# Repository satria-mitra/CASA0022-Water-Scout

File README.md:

<h1 align="center">Water Scout: A LoRaWAN-Based Water Height Monitoring and Visualization System for Urban Waterways</h1>

A dissertation for an [MSc Connected Environments](https://www.ucl.ac.uk/prospective-students/graduate/taught-degrees/connected-environments-msc)
<p>Centre for Advanced Spatial Analysis, Bartlett Faculty of the Built Environment</p>
<p>University College London </p>

##

This project utilised an Arduino 1310 with LoRaWAN communication and Ultrasonic sensor to monitor the water level of the River Lea that flows below the House Mill. The data observed then transmitted to The Things Network and published to MQTT Client. A 3D visualisation web page using WebXR was built to display the water level of The House Mill in 3D scene. The House Mill was created by [Dr. Gai Jorayev ](https://www.ucl.ac.uk/archaeology/people/gai-jorayev) and published on [Sketchfab](https://sketchfab.com/3d-models/house-mill-in-2019-c87dd07ab29f474aa491c88bc6b4956f). [The 3D visualisations web page](https://casa-0022-water-scout.vercel.app/) was hosted in the cloud for accessibility

|                         Water Scout                           |                3D Visualisations                 |
| :----------------------------------------------------------: | :-------------------------------------------: |
|  |  |

## Repository Content Summary

1. **3D Parts**

   This folder includes the 3D printed parts, namely Fusion360 project files and STLs for the enclosures and the 3D objects for the Data Table.

   - [Water Scout Enclosure](</3D Parts/Enclosure>)
   - [Solar Panel](</3D Parts/Solar Panel/>)

2. **Arduino**

   Includes code during calibration mode, and Water Scout device

   - [DYP-A01](/Arduino/DYP-A01)

3. **Schematics**

   The final schematics including PCB Gerber file used for this project. 
   
4. **Docs**

   This folder holds the page for the Water Scout web pages, including device introduction, 3D Visualisation page and VR mode for Connected Environment exhibition

5. **Dashboard**

   The configuration file for Node Red, Influxdb and Grafana 

6. **Supporting Documents**

   The extra files from the dissertation report, including Lab Testing, Deployment Test, and analysis

## Project Overview

<p align="center">Final prototype</p>

## Building

### Used components and tools

Hardware:

* [Arduino MKR WAN 1310](https://docs.arduino.cc/hardware/mkr-wan-1310): microcontroller with LoRa connectivity.
* [DYP-A01](https://www.dypcn.com/high-performance-ultrasonic-precision-rangefinder-dyp-a01-product/): a weatherproof humidity and temperature sensor.
* [Adafruit Solar Charger](https://www.adafruit.com/product/4755): a solar charger module
* [Adafruit Lipo Battery Gauge](https://www.adafruit.com/product/5580)
* [Solar panel](https://coolcomponents.co.uk/products/solar-panel-1-watt): 1 Watt, 10x80 cm.
* 2000 mA 3.7v battery

Software:

 - [InfluxDB](https://www.influxdata.com/)
 - [Telegraf](https://www.influxdata.com/time-series-platform/telegraf/)
 - [Grafana](https://grafana.com/)
 - [Docker Compose](https://docs.docker.com/compose/)

All the software applications are packed into one using Docker

## Results

#### The 3D Visualisations

<p align="center">3D Visualisations scene</p>

Click here for [3D Visualisations](https://casa-0022-water-scout.vercel.app/visualisation.html)

#### VR Mode for exhibition

<p align="center">3D Visualisations scene</p>

Click here for [VR Mode](https://casa-0022-water-scout.vercel.app/arjs.html)

## Credits

This project was built with inspiration and support from several open-source projects and contributions.

Special thanks to [CASA CE](https://github.com/ucl-casa-ce) team especially for the [Artes](https://github.com/ucl-casa-ce/artes) repository which was instrumental in creating the VR mode for the Water Scout project. Portions of the code for the VR mode were adapted and modified from his project.

Additionally, thanks to the open-source communities and contributors behind the following software and tools, which were essential in the development of this project:

- Arduino
- The Things Network
- InfluxDB
- Grafana
- Docker

## License

###### The software side is licensed under MIT License

```
MIT License

Permission is hereby granted, free of charge, to any person obtaining a copy
of this software and associated documentation files (the "Software"), to deal
in the Software without restriction, including without limitation the rights
to use, copy, modify, merge, publish, distribute, sublicense, and/or sell
copies of the Software, and to permit persons to whom the Software is
furnished to do so, subject to the following conditions:

The above copyright notice and this permission notice shall be included in all
copies or substantial portions of the Software.

THE SOFTWARE IS PROVIDED "AS IS", WITHOUT WARRANTY OF ANY KIND, EXPRESS OR
IMPLIED, INCLUDING BUT NOT LIMITED TO THE WARRANTIES OF MERCHANTABILITY,
FITNESS FOR A PARTICULAR PURPOSE AND NONINFRINGEMENT. IN NO EVENT SHALL THE
AUTHORS OR COPYRIGHT HOLDERS BE LIABLE FOR ANY CLAIM, DAMAGES OR OTHER
LIABILITY, WHETHER IN AN ACTION OF CONTRACT, TORT OR OTHERWISE, ARISING FROM,
OUT OF OR IN CONNECTION WITH THE SOFTWARE OR THE USE OR OTHER DEALINGS IN THE
SOFTWARE.
```

###### The hardware side is licensed under CERN License

```
This documentation describes Open Hardware and is licensed under the CERN OHL v. 1.2.

You may redistribute and modify this documentation under the terms of the CERN OHL v.1.2. (http://ohwr.org/cernohl). This documentation is distributed WITHOUT ANY EXPRESS OR IMPLIED WARRANTY, INCLUDING OF MERCHANTABILITY, SATISFACTORY QUALITY AND FITNESS FOR A PARTICULAR PURPOSE. Please see the CERN OHL v.1.2 for applicable conditions
```

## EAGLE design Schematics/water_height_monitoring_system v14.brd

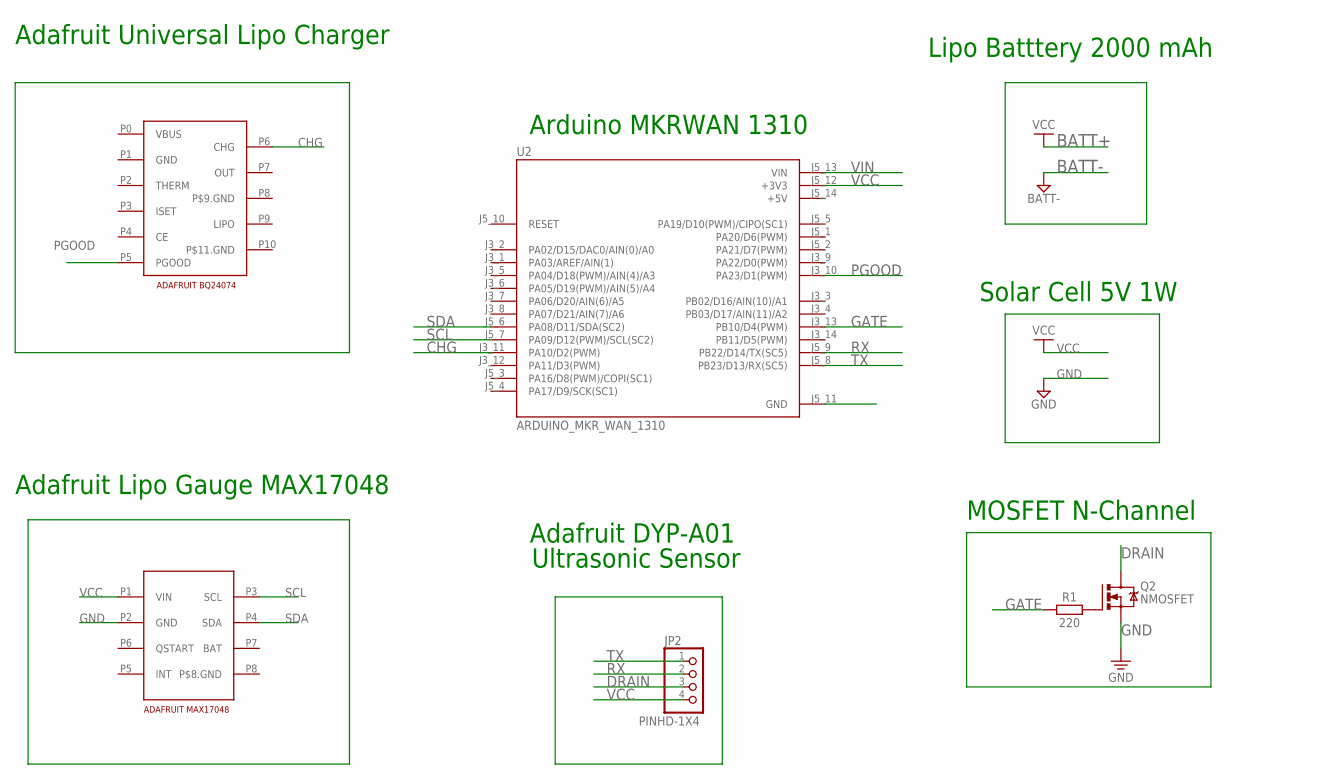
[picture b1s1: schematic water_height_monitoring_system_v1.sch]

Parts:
JP2: PINHD-1X4; 1X04
Q2: NMOSFET; TO220BV
R1: 220; RESAD724W46L381D178B
U2: ARDUINO_MKR_WAN_1310; BOARD_ARDUINO_MKR_WAN_1310
U$2: ADAFRUIT_BQ24074; BQ24074_MODULE
U$3: ADAFRUIT_MAX17048; MAX17048

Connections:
+5V: U2.J5_14 (+5V)
BAT: U$3.P7 (BAT)
CHG: U2.J3_11 (PA10/D2(PWM)), U$2.P6 (CHG)
DRAIN: JP2.3, Q2.D
GATE: R1.1, U2.J3_13 (PB10/D4(PWM))
LIPO: U$2.P9 (LIPO)
unnamed: Q2.G, R1.2
P$8.GND: U$3.P8 (P$8.GND)
P$9.GND: U$2.P8 (P$9.GND)
P$11.GND: U$2.P10 (P$11.GND)
PGOOD: U2.J3_10 (PA23/D1(PWM)), U$2.P5 (PGOOD)
RX: JP2.2, U2.J5_9 (PB22/D14/TX(SC5))
SCL: U2.J5_7 (PA09/D12(PWM)/SCL(SC2)), U$3.P3 (SCL)
SDA: U2.J5_6 (PA08/D11/SDA(SC2)), U$3.P4 (SDA)
TX: JP2.1, U2.J5_8 (PB23/D13/RX(SC5))
VBUS: U$2.P0 (VBUS)
VCC: JP2.4, U2.J5_12 (+3V3), U$3.P1 (VIN)
VIN: U2.J5_13 (VIN)

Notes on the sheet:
Adafruit Universal Lipo Charger
Adafruit Lipo Gauge MAX17048
Arduino MKRWAN 1310
Lipo Batttery 2000 mAh
Solar Cell 5V 1W
MOSFET N-Channel
Adafruit DYP-A01 Ultrasonic Sensor

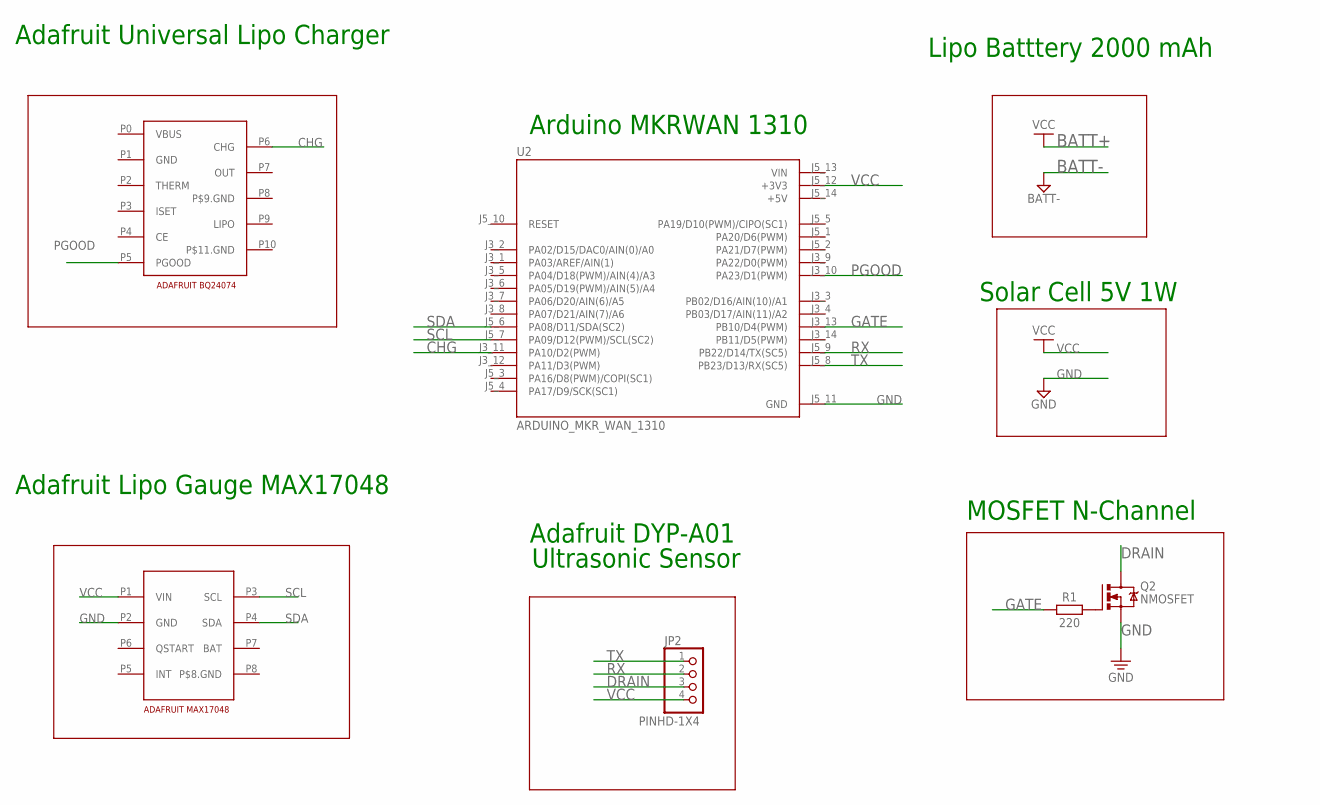
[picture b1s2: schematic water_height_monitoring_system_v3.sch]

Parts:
JP2: PINHD-1X4; 1X04
Q2: NMOSFET; TO220BV
R1: 220; RESAD724W46L381D178B
U2: ARDUINO_MKR_WAN_1310; BOARD_ARDUINO_MKR_WAN_1310
U$2: ADAFRUIT_BQ24074; BQ24074_MODULE
U$3: ADAFRUIT_MAX17048; MAX17048

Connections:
+5V: U2.J5_14 (+5V)
BAT: U$3.P7 (BAT)
CHG: U2.J3_11 (PA10/D2(PWM)), U$2.P6 (CHG)
DRAIN: JP2.3, Q2.D
GATE: R1.1, U2.J3_13 (PB10/D4(PWM))
LIPO: U$2.P9 (LIPO)
unnamed: Q2.G, R1.2
P$8.GND: U$3.P8 (P$8.GND)
P$9.GND: U$2.P8 (P$9.GND)
P$11.GND: U$2.P10 (P$11.GND)
PGOOD: U2.J3_10 (PA23/D1(PWM)), U$2.P5 (PGOOD)
RX: JP2.2, U2.J5_9 (PB22/D14/TX(SC5))
SCL: U2.J5_7 (PA09/D12(PWM)/SCL(SC2)), U$3.P3 (SCL)
SDA: U2.J5_6 (PA08/D11/SDA(SC2)), U$3.P4 (SDA)
TX: JP2.1, U2.J5_8 (PB23/D13/RX(SC5))
VBUS: U$2.P0 (VBUS)
VCC: JP2.4, U2.J5_12 (+3V3), U$3.P1 (VIN)

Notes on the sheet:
Adafruit Universal Lipo Charger
Adafruit Lipo Gauge MAX17048
Arduino MKRWAN 1310
Lipo Batttery 2000 mAh
Solar Cell 5V 1W
MOSFET N-Channel
Adafruit DYP-A01 Ultrasonic Sensor

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
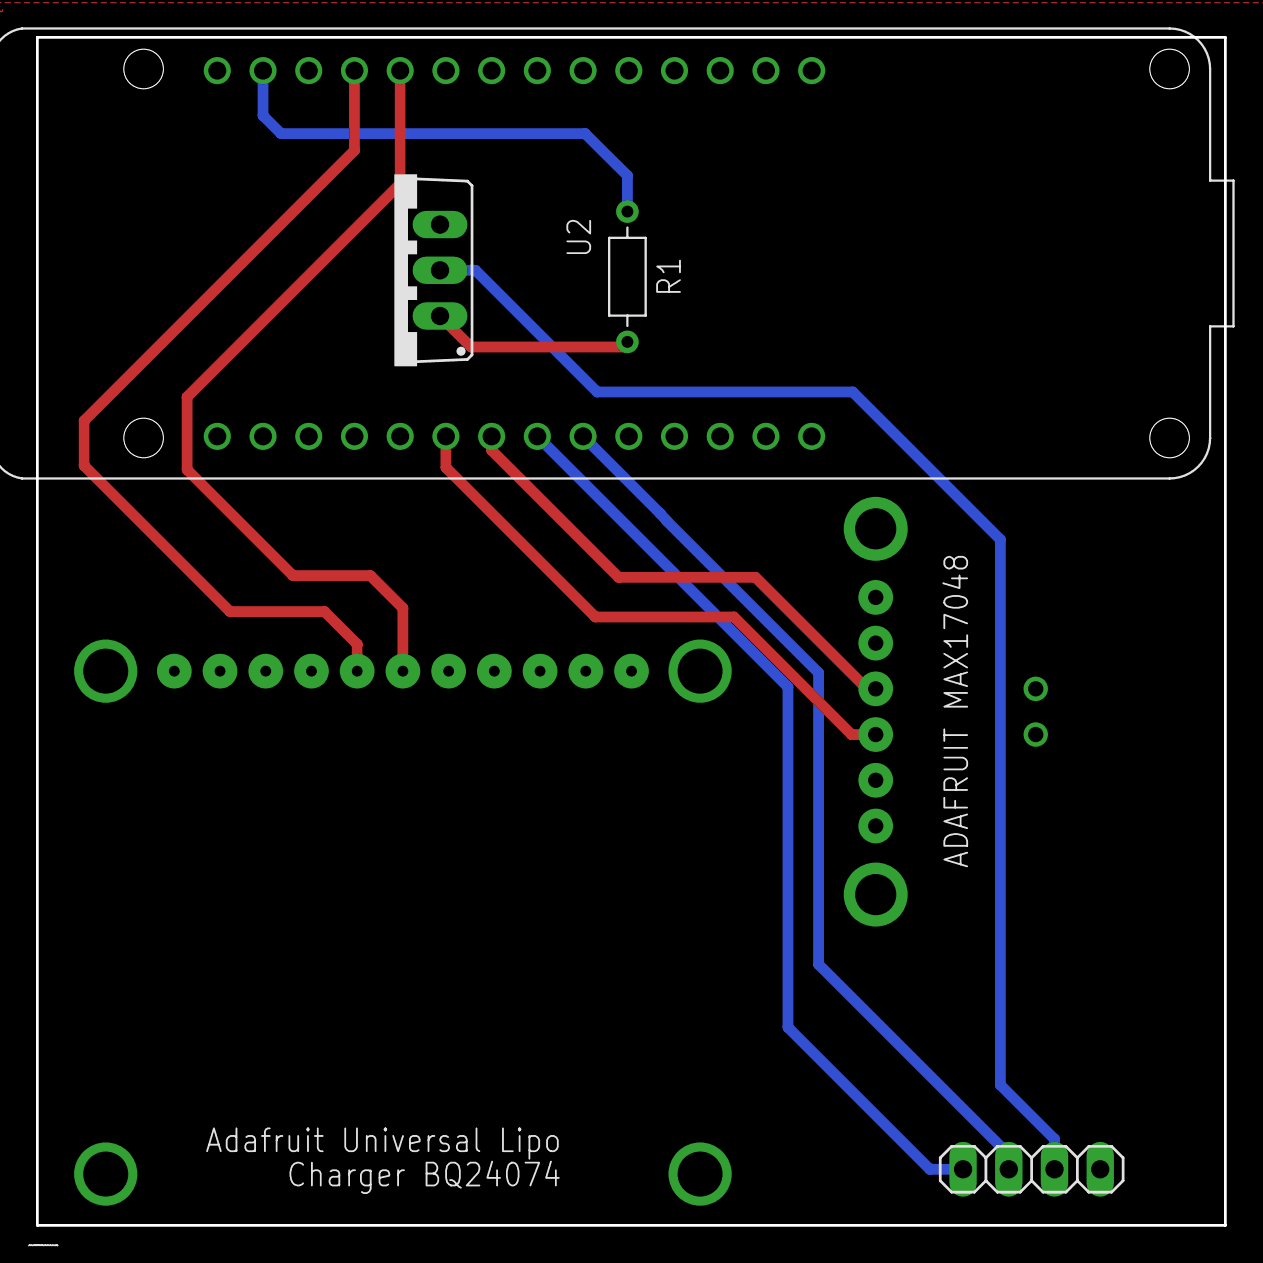
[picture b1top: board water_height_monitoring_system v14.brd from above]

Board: 2 copper layers, 66.0 x 66.0 mm, 6 parts (0 on the bottom side), 11 nets.

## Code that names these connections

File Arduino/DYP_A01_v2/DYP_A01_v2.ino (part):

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
/******** Pin, Variables and Class for Solar Charge Controller **********/
// Pin definitions for charge controller
#define PGOOD_PIN 1  // Power Good status pin
#define CHG_PIN 2    // Charge status pin

// Number of samples to take for determining status
#define CHARGE_SAMPLES 10
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
/******** Pin, Variables and Class for Ultrasonic Sensor **********/

const int sensorPowerPin = 4; // Pin to control MOSFET gate
int interval = 57000; // Interval to wake up (60000 milliseconds or 60 seconds)

class DYP_A01 {
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
  // Take multiple samples to determine status
  for (int i = 0; i < CHARGE_SAMPLES; i++) {
    pgood_count += digitalRead(PGOOD_PIN) == LOW ? 1 : 0;
    chg_count += digitalRead(CHG_PIN) == LOW ? 1 : 0;
    delay(SAMPLE_DELAY);
  }

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
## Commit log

2024-05-16 commit test code
2024-05-22 initial commit for adafruit DYP A01 ultrasonic sensor
2024-05-22 reduce reading interval to 10s
2024-05-22 add function to write to display
2024-05-22 use adafruit code
2024-05-22 add oled
2024-05-26 add function to send data to lora
2024-05-26 remove serial print each second
2024-05-26 fix gitignore
2024-05-26 fix arduino secrets
2024-05-30 Update sensor reading
2024-05-30 config lora connection
2024-05-30 apply deep sleep lib
2024-06-10 add mosfets to switch on off sensor
2024-06-10 commit telegraf config file
2024-06-12 uncomment power saving mode
2024-06-12 add function to monitor solar charger
2024-06-12 Reformat structure
2024-06-12 add init and downlink lorawan functions
2024-06-12 create functions to read sensor
2024-06-12 fix the payload message
2024-06-12 fix the payload for solar charger
2024-06-12 create function to conserve power
2024-06-13 trying downlink function
2024-06-19 add adafruit max17048 module
2024-06-19 add back up code
2024-06-19 why is there this file
2024-06-19 try to fix downlink function to reset board
2024-07-03 upload schematics and board eagle files
2024-07-03 upload gerber files
2024-07-03 upload enclosure model
2024-07-03 upload casa logo
2024-07-03 upload calibrator code
2024-07-03 update calibration mode
2024-07-11 fix charging logic
2024-07-11 Testing code with oled display
2024-08-15 fix files didnt commited properly
2024-08-15 commit web page for the project
2024-08-15 update github page
2024-08-15 test
2024-08-15 update the web to add webxr toggle
2024-08-15 test page
2024-08-15 test arjs
2024-08-16 deploy on vercel
2024-08-16 fix vercel app
2024-08-16 update modules
2024-08-16 remove unwanted files
2024-08-16 fix the files for deployment
2024-08-19 update 3d viz
2024-08-19 upload web page
2024-08-19 update for vercel
2024-08-19 add vercel
2024-08-19 update vercel json
2024-08-19 update vercel config
2024-08-19 vercel app
2024-08-19 update housemill model
2024-08-19 fix model
2024-08-19 smaller model
2024-08-19 upload git attributes
2024-08-19 update attributes
2024-08-19 upload new model
2024-08-23 fix 3d viz
2024-08-23 fix var name
2024-08-23 uncommit
2024-08-23 add dissertation data
2024-08-23 fix water calculation
2024-08-26 fix water body & ar
2024-08-26 fix chart
2024-08-30 upload assets
2024-08-30 upload readme files

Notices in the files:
parts and their libraries:
SparkFun-Aesthetics: Licensing: Creative Commons ShareAlike 4.0 International - https://creativecommons.org/licenses/by-sa/4.0
